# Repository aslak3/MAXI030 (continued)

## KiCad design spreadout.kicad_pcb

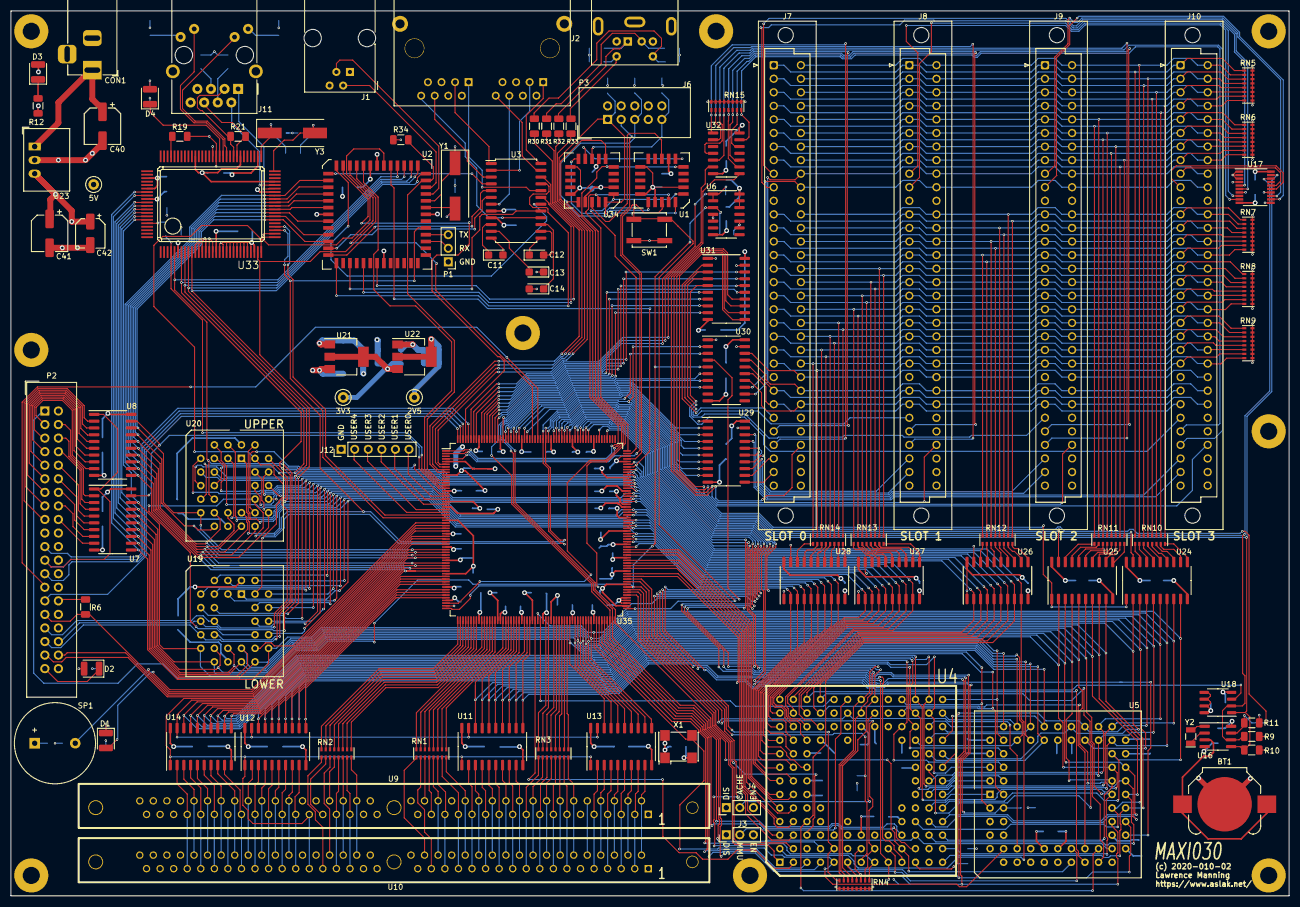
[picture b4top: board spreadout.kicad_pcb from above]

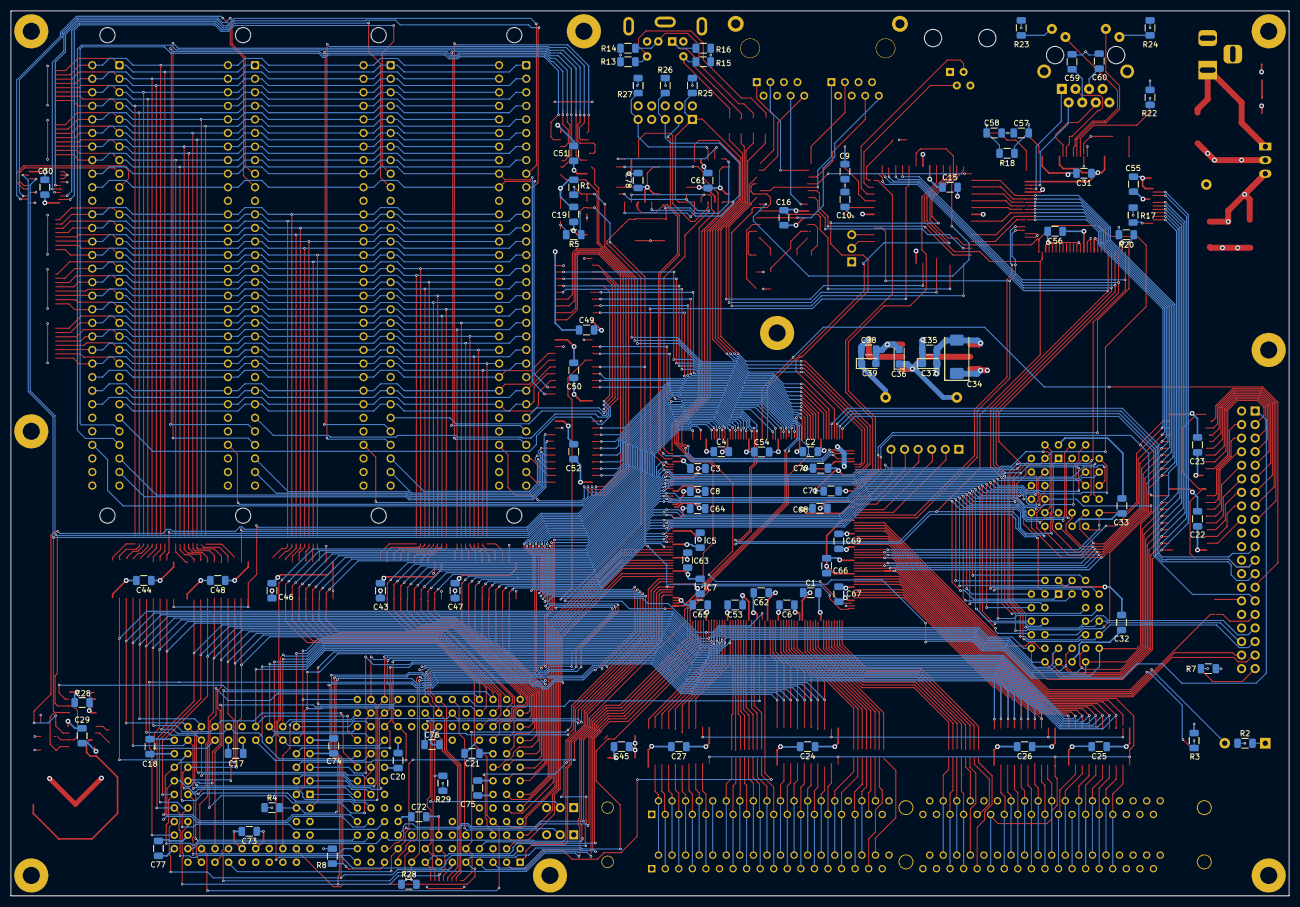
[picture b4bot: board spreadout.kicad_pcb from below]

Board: 4 copper layers, 239.4 x 165.7 mm, 199 parts (93 on the bottom side), 441 nets.

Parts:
BT1: Battery_Cell; BatteryHolder_Keystone_3000_1x12mm
C1, C2, C3, C4, C5, C6, C7, C8, C15, C16, C17, C18, C19, C20, C21, C22, C23, C24, C25, C26, C27, C28, C29, C30, C31, C32, C33, C35, C38, C43, C44, C45, C46, C47, C48, C49, C50, C51, C52, C53, C54, C55, C56, C61, C62, C63, C64, C65, C66, C67, C68, C69, C70, C71, C72, C73, C74, C75, C76, C77, C78: 0.1u; C_1206_3216Metric
C9, C10, C57, C58: 22p; C_1206_3216Metric
C11, C12, C13, C14: 1.0u; CP_EIA-3216-18_Kemet-A
C34: 47u; CP_EIA-7343-15_Kemet-W
C36, C37, C39: 10u; CP_EIA-3216-10_Kemet-I
C40: 470u; CP_Elec_6.3x7.7
C41: 220u; CP_Elec_6.3x7.7
C42: 10u; CP_Elec_5x5.7
C59, C60: 10n; C_1206_3216Metric
CON1: POWERLJACK; BarrelJack_Horizontal
D1: CORELED; LED_1210_3225Metric
D2: IDELED; LED_1210_3225Metric
D3: POWERLED; LED_1210_3225Metric
D4: LED; LED_1210_3225Metric
H1, H2, H3, H4, H5, H6, H7, H8, H9: MountingHole_Pad; MountingHole_3.2mm_M3_Pad
J1: RJ10_KEYBOARD; RJ10
J2: DUALRJ45_RS232; DUALRJ45
J3, J4: Conn_01x03; PinHeader_1x03_P2.54mm_Vertical
J6: Mini-DIN-6; Connector_Mini-DIN_Female_6Pin_2rows
J7, J8, J9, J10: DIN_41612_3x32_MIDI020_EXP; DIN41612_C_2x32_Female_Vertical_THT
J11: RJ45_Amphenol_RJMG1BD3B8K1ANR
J12: Conn_01x06; PinHeader_1x06_P2.54mm_Vertical
P1: TTL_SERIAL; PinHeader_1x03_P2.54mm_Vertical
P2: CONN_02X20_IDE; IDC-Header_2x20_P2.54mm_Vertical
P3: JTAG; IDC-Header_2x05_P2.54mm_Vertical
R1, R4, R5, R6, R8, R9, R10, R11, R13, R14, R15, R16, R28, R29, R34: 4.7K; R_1206_3216Metric
R2, R3, R7, R12, R20, R22, R23, R24, R25, R26, R27: 1K; R_1206_3216Metric
R17: 27K; R_1206_3216Metric
R18: 1M; R_1206_3216Metric
R19: 10K; R_1206_3216Metric
R21: 200; R_1206_3216Metric
R30, R31, R32, R33: 120; R_1206_3216Metric
RN1, RN2, RN3, RN10, RN11, RN12, RN13, RN14: 33; R_Cat16-8
RN4, RN15: 4.7K; R_Cat16-8
RN5, RN6, RN7, RN8, RN9: 10K; R_Cat16-8
SP1: BUZZER; Buzzer_15x7.5RM7.6
SW1: RESETBUTTON; SW_Push_1P1T_NO_CK_KSC6xxJ
TP1: 3V3; TestPoint_Loop_D1.80mm_Drill1.0mm_Beaded
TP2: 2V5; TestPoint_Loop_D1.80mm_Drill1.0mm_Beaded
TP3: 5V; TestPoint_Loop_D1.80mm_Drill1.0mm_Beaded
U1, U34: EPC2; PLCC-20
U2: SC26C94; PLCC-52
U3: MAX238; SOIC-24W_7.5x15.4mm_P1.27mm
U4: MC68030RC; PGA128
U5: 68882; PLCC-68_THT-Socket
U6: 74LS03; SOIC-14_3.9x8.7mm_P1.27mm
U7, U8, U24, U25, U26, U27, U28, U29, U30, U31: 74HCT245; SO-20_5.3x12.6mm_P1.27mm
U9, U10: SIM72Pin; SIMM72Pins
U11, U12, U13, U14: 74HC245; SO-20_5.3x12.6mm_P1.27mm
U16: LM75A; SO-8_3.9x4.9mm_P1.27mm
U17: PCA9544APW; TSSOP-20_4.4x6.5mm_P0.65mm
U18: DS1307Z+; SOIC-8_3.9x4.9mm_P1.27mm
U19, U20: SST39SF040-PC32; PLCC-32_THT-Socket
U21: AZ1117-3.3; SOT-223-3_TabPin2
U22: AZ1117-2.5; SOT-223-3_TabPin2
U23: SR05S05; Converter_DCDC_RECOM_R-78E-0.5_THT
U32: 74LS21; SOIC-14_3.9x8.7mm_P1.27mm
U33: RTL8019AS
U35: EPF10K130EQC240; PQFP-240_32.1x32.1mm_P0.5mm
X1: MPUOSC; Oscillator_SMD_SeikoEpson_SG8002CA-4Pin_7.0x5.0mm
Y1: 7.3728M; Crystal_SMD_HC49-SD
Y2: 32.768; Crystal_SMD_EuroQuartz_EQ161-2Pin_3.2x1.5mm
Y3: 20M; Crystal_SMD_HC49-SD

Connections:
+2V5: C1.1, C3.1, C5.1, C7.1, C38.1, C39.1, C53.1, C62.1, C64.1, C66.1, C68.1, C70.1, TP2.1, U22.2, U35.5, U35.20, U35.27, U35.47, U35.76, U35.89, U35.96, U35.122, U35.130, U35.150, U35.159, U35.170
+3V3: C2.1, C4.1, C6.1, C8.1, C35.1, C36.1, C37.1, C54.1, C61.1, C63.1, C65.1, C67.1, C69.1, C71.1, C78.1, P3.4, R26.1, R27.1, TP1.1, U1.5, U1.14, U1.18, U1.20, U21.2, U22.3, U34.5, U34.14, U34.18, U34.20, U35.16, U35.37, U35.57, U35.59, U35.77, U35.112, U35.140, U35.160, U35.189, U35.205, U35.224
+5VD: C13.1, C15.1, C16.1, C17.1, C18.1, C19.1, C20.1, C21.1, C22.1, C23.1, C24.1, C25.1, C26.1, C27.1, C28.1, C29.1, C30.1, C31.1, C32.1, C33.1, C34.1, C41.1, C42.1, C43.1, C44.1, C45.1, C46.1, C47.1, C48.1, C49.1, C50.1, C51.1, C52.1, C55.1, C56.1, C72.1, C73.1, C74.1, C75.1, C76.1, C77.1, D3.2, J1.1, J3.1, J4.1, J6.4, J7.c11, J7.c32, J8.c11, J8.c32, J9.c11, J9.c32, J10.c11, J10.c32, P2.20, R1.1, R4.1, R5.2, R7.1, R8.1, R9.1, R10.1, R11.1, R13.2, R14.2, R15.2, R16.2, R22.1, R23.2, R24.2, R28.1, R29.1, R34.2, RN4.9, RN4.10, RN4.11, RN4.12, RN4.13, RN4.14, RN4.15, RN4.16, RN5.9, RN5.10, RN5.11, RN5.12, RN5.13, RN5.14, RN5.15, RN5.16, RN6.9, RN6.10, RN6.11, RN6.12, RN6.13, RN6.14, RN6.15, RN6.16, RN7.9, RN7.10, RN7.11, RN7.12, RN7.13, RN7.14, RN7.15, RN7.16, RN8.9, RN8.10, RN8.11, RN8.12, RN8.13, RN8.14, RN8.15, RN8.16, RN9.9, RN9.10, RN9.11, RN9.12, RN9.13, RN9.14, RN9.15, RN9.16, RN15.9, RN15.10, RN15.11, RN15.12, RN15.13, RN15.14, RN15.15, RN15.16, TP3.1, U2.2, U3.9, U4.C6, U4.D4, U4.D10, U4.F2, U4.F11, U4.H3, U4.H11, U4.K4, U4.K10, U4.L6, U5.10, U5.16, U5.17, U5.18, U5.26, U5.27, U5.43, U5.52, U5.53, U5.61, U6.4, U6.5, U6.9, U6.10, U6.12, U6.13, U6.14, U7.20, U8.20, U9.10, U9.30, U9.59, U10.10, U10.30, U10.59, U11.20, U12.20, U13.20, U14.20, U16.5, U16.6, U16.7, U16.8, U17.4, U17.7, U17.11, U17.14, U17.20, U18.8, U19.32, U20.32, U21.3, U23.3, U24.20, U25.20, U26.1, U26.20, U27.1, U27.20, U28.1, U28.20, U29.1, U29.20, U30.1, U30.20, U31.1, U31.20, U32.14, U33.6, U33.15, U33.16, U33.17, U33.31, U33.32, U33.47, U33.57, U33.65, U33.70, U33.89, X1.1, X1.4
/FPGA/USER0: J12.6, U35.18
/FPGA/USER1: J12.5, U35.19
/FPGA/USER2: J12.4, U35.21
/FPGA/USER3: J12.3, U35.23
/FPGA/USER4: J12.2, U35.24
/IDE/IDED0: P2.4, U7.2
/IDE/IDED1: P2.6, U7.3
/IDE/IDED2: P2.8, U7.4
/IDE/IDED3: P2.10, U7.5
/IDE/IDED4: P2.12, U7.6
/IDE/IDED5: P2.14, U7.7
/IDE/IDED6: P2.16, U7.8
/IDE/IDED7: P2.18, U7.9
/IDE/IDED8: P2.17, U8.2
/IDE/IDED9: P2.15, U8.3
/IDE/IDED10: P2.13, U8.4
/IDE/IDED11: P2.11, U8.5
/IDE/IDED12: P2.9, U8.6
/IDE/IDED13: P2.7, U8.7
/IDE/IDED14: P2.5, U8.8
/IDE/IDED15: P2.3, U8.9
/SIMM/SD0: U9.2, U10.2, U13.9
/SIMM/SD1: U9.4, U10.4, U13.7
/SIMM/SD2: U9.6, U10.6, U13.5
/SIMM/SD3: U9.8, U10.8, U13.3
/SIMM/SD4: U9.20, U10.20, U11.9
/SIMM/SD5: U9.22, U10.22, U11.7
/SIMM/SD6: U9.24, U10.24, U11.5
/SIMM/SD7: U9.26, U10.26, U11.3
/SIMM/SD8: U9.49, U10.49, U12.9
/SIMM/SD9: U9.51, U10.51, U12.7
/SIMM/SD10: U9.53, U10.53, U12.5
/SIMM/SD11: U9.55, U10.55, U12.3
/SIMM/SD12: U9.57, U10.57, U14.9
/SIMM/SD13: U9.61, U10.61, U14.6
/SIMM/SD14: U9.63, U10.63, U14.4
/SIMM/SD15: U9.65, U10.65, U14.2
/SIMM/SD16: U9.3, U10.3, U13.8
/SIMM/SD17: U9.5, U10.5, U13.6
/SIMM/SD18: U9.7, U10.7, U13.4
/SIMM/SD19: U9.9, U10.9, U13.2
/SIMM/SD20: U9.21, U10.21, U11.8
/SIMM/SD21: U9.23, U10.23, U11.6
/SIMM/SD22: U9.25, U10.25, U11.4
/SIMM/SD23: U9.27, U10.27, U11.2
/SIMM/SD24: U9.50, U10.50, U12.8
/SIMM/SD25: U9.52, U10.52, U12.6
/SIMM/SD26: U9.54, U10.54, U12.4
/SIMM/SD27: U9.56, U10.56, U12.2
/SIMM/SD28: U9.58, U10.58, U14.8
/SIMM/SD29: U9.60, U10.60, U14.7
/SIMM/SD30: U9.62, U10.62, U14.5
/SIMM/SD31: U9.64, U10.64, U14.3
A0: U2.51, U4.A2, U26.9, U35.174
A1: U2.50, U4.C4, U5.25, U19.12, U20.12, U26.8, U33.5, U35.173
A2: P2.35, U2.49, U4.D13, U5.24, U19.11, U20.11, U26.7, U33.7, U35.172
A3: P2.33, U2.48, U4.D12, U5.23, U19.10, U20.10, U26.6, U33.8, U35.171
A4: P2.36, U2.47, U4.C13, U5.22, U19.9, U20.9, U26.5, U33.9, U35.169
A5: U2.46, U4.C12, U19.8, U20.8, U26.4, U33.10, U35.168
A6: U4.D11, U19.7, U20.7, U26.3, U35.167
A7: U4.B13, U19.6, U20.6, U26.2, U35.166
A8: U4.B12, U19.5, U20.5, U27.9, U35.164
A9: U4.C11, U19.27, U20.27, U27.8, U35.163
A10: U4.A13, U19.26, U20.26, U27.7, U35.162
A11: U4.C10, U19.23, U20.23, U27.6, U35.161
A12: U4.B11, U19.25, U20.25, U27.5, U35.158
A13: U4.A12, U19.4, U20.4, U27.4, U35.157
A14: U4.B10, U19.28, U20.28, U27.3, U35.156
A15: U4.A11, U19.29, U20.29, U27.2, U35.154
A16: U4.B9, U19.3, U20.3, U28.9, U35.153
A17: U4.A10, U19.2, U20.2, U28.8, U35.152
A18: U4.C8, U19.30, U20.30, U28.7, U35.151
A19: U4.A9, U19.1, U20.1, U28.6, U35.149
A20: U4.B8, U28.5, U35.148
A21: U4.A8, U28.4, U35.147
A22: U4.B7, U28.3, U35.146
A23: U4.A7, U28.2, U35.144
A24: U4.A6, U35.143
A25: U4.B6, U35.142
A26: U4.A5, U35.141
A27: U4.B5, U35.139
A28: U4.A4, U35.138
A29: U4.B4, U35.137
A30: U4.A3, U35.136
A31: U4.B3, U35.134
BUZZER: SP1.2, U35.30
CFCLOCK: U1.4, U34.4, U35.179
CFCONFIG: SW1.1, U34.13, U35.121
CFDATA: U1.2, U34.2, U35.180
CFDONE: U34.9, U35.2
CFSTATUS: U1.8, U34.8, U35.60
CFTOCORE: U1.1, U35.177
CORETOHEADER: P3.3, U35.4
CTSA232: J2.A8, U3.23
CTSB232: J2.B8, U3.16
D0: U4.K13, U5.3, U11.18, U35.80
D1: U4.K12, U5.2, U11.17, U35.81
D2: U4.L13, U5.1, U11.16, U35.82
D3: U4.M13, U5.68, U11.15, U35.83
D4: U4.L12, U5.67, U11.14, U35.84
D5: U4.K11, U5.66, U11.13, U35.86
D6: U4.M12, U5.65, U11.12, U35.87
D7: U4.L11, U5.64, U11.11, U35.88
D8: U4.N13, U5.62, U12.18, U35.48
D9: U4.M11, U5.60, U12.17, U35.49
D10: U4.L10, U5.59, U12.16, U35.50
D11: U4.N12, U5.58, U12.15, U35.51
D12: U4.M10, U5.57, U12.14, U35.53
D13: U4.N11, U5.56, U12.13, U35.54
D14: U4.M9, U5.55, U12.12, U35.55
D15: U4.N10, U5.54, U12.11, U35.56
D16: U4.N9, U5.50, U7.18, U13.18, U19.13, U24.2, U33.95, U35.103
D17: U4.M8, U5.49, U7.17, U13.17, U19.14, U24.3, U33.94, U35.105
D18: U4.N8, U5.48, U7.16, U13.16, U19.15, U24.4, U33.93, U35.106
D19: U4.N7, U5.47, U7.15, U13.15, U19.17, U24.5, U33.92, U35.107
D20: U4.M7, U5.46, U7.14, U13.14, U19.18, U24.6, U33.91, U35.108
D21: U4.N6, U5.45, U7.13, U13.13, U19.19, U24.7, U33.90, U35.109
D22: U4.M6, U5.44, U7.12, U13.12, U19.20, U24.8, U33.88, U35.110
D23: U4.N5, U5.42, U7.11, U13.11, U19.21, U24.9, U33.87, U35.111
D24: U2.18, U4.M5, U5.40, U8.18, U14.18, U20.13, U25.2, U33.36, U35.38
D25: U2.17, U4.N4, U5.39, U8.17, U14.17, U20.14, U25.3, U33.37, U35.39
D26: U2.15, U4.N3, U5.38, U8.16, U14.16, U20.15, U25.4, U33.38, U35.40
D27: U2.13, U4.M4, U5.37, U8.15, U14.15, U20.17, U25.5, U33.39, U35.41
D28: U2.12, U4.N2, U5.36, U8.14, U14.14, U20.18, U25.6, U33.40, U35.43
D29: U2.11, U4.M3, U5.35, U8.13, U14.13, U20.19, U25.7, U33.41, U35.44
D30: U2.10, U4.L4, U5.34, U8.12, U14.12, U20.20, U25.8, U33.42, U35.45
D31: U2.9, U4.N1, U5.33, U8.11, U14.11, U20.21, U25.9, U33.43, U35.46
ETHINT: R20.2, U33.4, U35.14
EXPA0: J7.a12, J8.a12, J9.a12, J10.a12, RN7.1, RN12.9
EXPA1: J7.c12, J8.c12, J9.c12, J10.c12, RN7.2, RN12.10
EXPA2: J7.a13, J8.a13, J9.a13, J10.a13, RN7.3, RN12.11
EXPA3: J7.c13, J8.c13, J9.c13, J10.c13, RN7.4, RN12.12
EXPA4: J7.a14, J8.a14, J9.a14, J10.a14, RN7.5, RN12.13
EXPA5: J7.c14, J8.c14, J9.c14, J10.c14, RN7.6, RN12.14
EXPA6: J7.a15, J8.a15, J9.a15, J10.a15, RN7.7, RN12.15
EXPA7: J7.c15, J8.c15, J9.c15, J10.c15, RN7.8, RN12.16
EXPA8: J7.a16, J8.a16, J9.a16, J10.a16, RN8.1, RN13.9
EXPA9: J7.c16, J8.c16, J9.c16, J10.c16, RN8.2, RN13.10
EXPA10: J7.a17, J8.a17, J9.a17, J10.a17, RN8.3, RN13.11
EXPA11: J7.c17, J8.c17, J9.c17, J10.c17, RN8.4, RN13.12
EXPA12: J7.a18, J8.a18, J9.a18, J10.a18, RN8.5, RN13.13
EXPA13: J7.c18, J8.c18, J9.c18, J10.c18, RN8.6, RN13.14
EXPA14: J7.a19, J8.a19, J9.a19, J10.a19, RN8.7, RN13.15
EXPA15: J7.c19, J8.c19, J9.c19, J10.c19, RN8.8, RN13.16
EXPA16: J7.a20, J8.a20, J9.a20, J10.a20, RN9.1, RN14.9
EXPA17: J7.c20, J8.c20, J9.c20, J10.c20, RN9.2, RN14.10
EXPA18: J7.a21, J8.a21, J9.a21, J10.a21, RN9.3, RN14.11
EXPA19: J7.c21, J8.c21, J9.c21, J10.c21, RN9.4, RN14.12
EXPA20: J7.a22, J8.a22, J9.a22, J10.a22, RN9.5, RN14.13
EXPA21: J7.c22, J8.c22, J9.c22, J10.c22, RN9.6, RN14.14
EXPA22: J7.a23, J8.a23, J9.a23, J10.a23, RN9.7, RN14.15
EXPA23: J7.c23, J8.c23, J9.c23, J10.c23, RN9.8, RN14.16
EXPD16: J7.a1, J8.a1, J9.a1, J10.a1, RN5.1, RN10.16
EXPD17: J7.c1, J8.c1, J9.c1, J10.c1, RN5.2, RN10.15
EXPD18: J7.a2, J8.a2, J9.a2, J10.a2, RN5.3, RN10.14
EXPD19: J7.c2, J8.c2, J9.c2, J10.c2, RN5.4, RN10.13
EXPD20: J7.a3, J8.a3, J9.a3, J10.a3, RN5.5, RN10.12
EXPD21: J7.c3, J8.c3, J9.c3, J10.c3, RN5.6, RN10.11
EXPD22: J7.a4, J8.a4, J9.a4, J10.a4, RN5.7, RN10.10
EXPD23: J7.c4, J8.c4, J9.c4, J10.c4, RN5.8, RN10.9
EXPD24: J7.a5, J8.a5, J9.a5, J10.a5, RN6.1, RN11.16
EXPD25: J7.c5, J8.c5, J9.c5, J10.c5, RN6.2, RN11.15
EXPD26: J7.a6, J8.a6, J9.a6, J10.a6, RN6.3, RN11.14
EXPD27: J7.c6, J8.c6, J9.c6, J10.c6, RN6.4, RN11.13
EXPD28: J7.a7, J8.a7, J9.a7, J10.a7, RN6.5, RN11.12
EXPD29: J7.c7, J8.c7, J9.c7, J10.c7, RN6.6, RN11.11
EXPD30: J7.a8, J8.a8, J9.a8, J10.a8, RN6.7, RN11.10
EXPD31: J7.c8, J8.c8, J9.c8, J10.c8, RN6.8, RN11.9
EXPMPUCLK: J7.a25, J8.a25, J9.a25, J10.a25, U30.16
EXPR~W: J7.c26, J8.c26, J9.c26, J10.c26, U30.14
EXPSCLE0: J7.a9, U17.6
EXPSCLE1: J8.a9, U17.9
EXPSCLE2: J9.a9, U17.13
EXPSCLE3: J10.a9, U17.16
EXPSDAE0: J7.a10, U17.5
EXPSDAE1: J8.a10, U17.8
EXPSDAE2: J9.a10, U17.12
EXPSDAE3: J10.a10, U17.15
FC0: U4.D2, U35.113
FC1: U4.C1, U35.114
FC2: U4.D1, U35.115
GNDA: BT1.2, C1.2, C2.2, C3.2, C4.2, C5.2, C6.2, C7.2, C8.2, C9.2, C10.2, C14.2, C15.2, C16.2, C17.2, C18.2, C19.2, C20.2, C21.2, C22.2, C23.2, C24.2, C25.2, C26.2, C27.2, C28.2, C29.2, C30.2, C31.2, C32.2, C33.2, C34.2, C35.2, C36.2, C37.2, C38.2, C39.2, C40.2, C41.2, C42.2, C43.2, C44.2, C45.2, C46.2, C47.2, C48.2, C49.2, C50.2, C51.2, C52.2, C53.2, C54.2, C55.2, C56.2, C57.1, C58.1, C59.2, C60.2, C61.2, C62.2, C63.2, C64.2, C65.2, C66.2, C67.2, C68.2, C69.2, C70.2, C71.2, C72.2, C73.2, C74.2, C75.2, C76.2, C77.2, C78.2, CON1.2, CON1.3, H1.1, H2.1, H3.1, H4.1, H5.1, H6.1, H7.1, H8.1, H9.1, J1.4, J2.A4, J2.A5, J2.B4, J2.B5, J2.GND, J3.3, J4.3, J6.3, J7.a11, J7.a32, J8.a11, J8.a32, J9.a11, J9.a32, J10.a11, J10.a32, J11.13, J11.R8, J12.1, P1.1, P2.2, P2.19, P2.22, P2.24, P2.26, P2.30, P2.40, P3.2, P3.10, R2.1, R3.1, R6.1, R12.2, R17.1, R19.1, R20.1, R25.2, SW1.2, U1.10, U2.1, U2.14, U2.28, U2.40, U3.8, U4.C5, U4.C7, U4.C9, U4.E3, U4.E11, U4.F3, U4.G3, U4.G11, U4.J3, U4.J11, U4.L5, U4.L7, U4.L8, U4.L9, U5.5, U5.6, U5.7, U5.8, U5.9, U5.12, U5.14, U5.19, U5.30, U5.41, U5.51, U5.63, U6.7, U7.10, U8.10, U9.1, U9.39, U9.72, U10.1, U10.39, U10.72, U11.10, U12.10, U13.10, U14.10, U16.4, U17.1, U17.2, U17.3, U17.10, U18.4, U19.16, U20.16, U21.1, U22.1, U23.2, U24.10, U25.10, U26.10, U26.19, U27.10, U27.19, U28.10, U28.19, U29.10, U29.19, U30.10, U30.19, U31.10, U31.19, U32.7, U33.11, U33.12, U33.13, U33.14, U33.18, U33.19, U33.20, U33.21, U33.22, U33.23, U33.24, U33.25, U33.26, U33.27, U33.28, U33.44, U33.52, U33.64, U33.83, U33.86, U34.10, U35.10, U35.22, U35.32, U35.42, U35.52, U35.69, U35.85, U35.93, U35.104, U35.123, U35.124, U35.125, U35.135, U35.145, U35.155, U35.165, U35.176, U35.178, U35.197, U35.216, U35.232, X1.2
HEADERTOCF: P3.9, R27.2, U34.11
IDEIRQ: P2.31, R6.2, U35.31
LED: D1.2, U35.29
MPUCLK: U4.E1, U5.11, U30.4, U35.91, X1.3
unnamed: BT1.1, U18.3
unnamed: C9.1, U2.42, Y1.1
unnamed: C10.1, U2.41, Y1.2
unnamed: C11.1, U3.10
unnamed: C11.2, U3.12
unnamed: C12.1, U3.13
unnamed: C12.2, U3.14
unnamed: C13.2, U3.11
unnamed: C14.1, U3.15
unnamed: C40.1, CON1.1, U23.1
unnamed: C57.2, R18.2, U33.51, Y3.1
unnamed: C58.2, R18.1, U33.50, Y3.2
unnamed: C59.1, J11.R4
unnamed: C60.1, J11.R5
unnamed: D1.1, R3.2
unnamed: D2.1, P2.39
unnamed: D2.2, R7.2
unnamed: D3.1, R12.1
unnamed: D4.1, U33.63
unnamed: D4.2, R22.2
unnamed: J1.2, U2.44
unnamed: J1.3, U2.43
unnamed: J6.1, R16.1, R32.1
unnamed: J6.2, R14.1, R31.2
unnamed: J6.5, R15.1, R33.1
unnamed: J6.6, R13.1, R30.2
unnamed: J11.L1, R24.1
unnamed: J11.L2, U33.62
unnamed: J11.L3, U33.61
unnamed: J11.L4, R23.1
unnamed: J11.R1, U33.45
unnamed: J11.R2, U33.46
unnamed: J11.R3, R21.1, U33.59
unnamed: J11.R6, R21.2, U33.58
unnamed: P1.2, U2.36
unnamed: P1.3, U2.37
unnamed: R2.2, SP1.1
unnamed: R17.2, U33.96
unnamed: R19.2, U33.77
unnamed: RN1.1, U35.79
unnamed: RN1.2, U35.78
unnamed: RN1.3, U35.75
unnamed: RN1.4, U35.74
unnamed: RN1.5, U35.73
unnamed: RN1.6, U35.72
unnamed: RN1.7, U35.71
unnamed: RN1.8, U35.70
unnamed: RN2.1, U35.68
unnamed: RN2.2, U35.67
unnamed: RN2.3, U35.66
unnamed: RN2.4, U35.65
unnamed: RN2.5, U35.64
unnamed: RN2.6, U35.63
unnamed: RN2.7, U35.62
unnamed: RN2.8, U35.61
unnamed: RN3.1, U35.102
unnamed: RN3.2, U35.101
unnamed: RN3.3, U35.100
unnamed: RN3.4, U35.99
unnamed: RN3.5, U35.98
unnamed: RN3.6, U35.97
unnamed: RN3.7, U35.95
unnamed: RN3.8, U35.94
unnamed: RN10.1, U24.18
unnamed: RN10.2, U24.17
unnamed: RN10.3, U24.16
unnamed: RN10.4, U24.15
unnamed: RN10.5, U24.14
unnamed: RN10.6, U24.13
unnamed: RN10.7, U24.12
unnamed: RN10.8, U24.11
unnamed: RN11.1, U25.18
unnamed: RN11.2, U25.17
unnamed: RN11.3, U25.16
unnamed: RN11.4, U25.15
unnamed: RN11.5, U25.14
unnamed: RN11.6, U25.13
unnamed: RN11.7, U25.12
unnamed: RN11.8, U25.11
unnamed: RN12.1, U26.18
unnamed: RN12.2, U26.17
unnamed: RN12.3, U26.16
unnamed: RN12.4, U26.15
unnamed: RN12.5, U26.14
unnamed: RN12.6, U26.13
unnamed: RN12.7, U26.12
unnamed: RN12.8, U26.11
unnamed: RN13.1, U27.18
unnamed: RN13.2, U27.17
unnamed: RN13.3, U27.16
unnamed: RN13.4, U27.15
unnamed: RN13.5, U27.14
unnamed: RN13.6, U27.13
unnamed: RN13.7, U27.12
unnamed: RN13.8, U27.11
unnamed: RN14.1, U28.18
unnamed: RN14.2, U28.17
unnamed: RN14.3, U28.16
unnamed: RN14.4, U28.15
unnamed: RN14.5, U28.14
unnamed: RN14.6, U28.13
unnamed: RN14.7, U28.12
unnamed: RN14.8, U28.11
unnamed: U1.9, U34.12
unnamed: U1.11, U34.1
unnamed: U2.7, U3.18
unnamed: U2.8, U3.4
unnamed: U2.19, U3.6
unnamed: U2.20, U3.5
unnamed: U2.21, U3.21
unnamed: U2.23, U3.17
unnamed: U2.25, U3.19
unnamed: U2.27, U3.22
unnamed: U18.1, Y2.2
unnamed: U18.2, Y2.1
PS2ACLK: R33.2, U35.6
PS2ADATA: R32.2, U35.7
PS2BCLK: R30.1, U35.9
PS2BDATA: R31.1, U35.8
RESET: U2.38, U33.33, U35.26
RTCSQWAVE: R11.2, U18.7, U35.206
RTSA232: J2.A1, U3.24
RTSB232: J2.B1, U3.20
RXA232: J2.A6, U3.7
RXB232: J2.B6, U3.3
R~W: U4.L3, U5.28, U30.6, U35.118
SA0: RN3.16, U9.12, U10.12
SA1: RN3.15, U9.13, U10.13
SA2: RN3.14, U9.14, U10.14
SA3: RN3.13, U9.15, U10.15
SA4: RN3.12, U9.16, U10.16
SA5: RN3.11, U9.17, U10.17
SA6: RN3.10, U9.18, U10.18
SA7: RN1.16, U9.28, U10.28
SA8: RN1.14, U9.31, U10.31
SA9: RN1.13, U9.32, U10.32
SA10: RN3.9, U9.19, U10.19
SA11: RN1.15, U9.29, U10.29
SCL: R9.2, U16.2, U17.18, U18.6, U35.202
SDA: R10.2, U16.1, U17.19, U18.5, U35.201
SIZ0: U4.L2, U35.116
SIZ1: U4.K3, U35.117
SYSCLEAR: R1.2, U6.1, U6.2, U35.233
TCK: P3.1, R25.1, U1.3, U34.3, U35.1
TEMPALERT: U16.3, U35.133
TMS: P3.5, R26.2, U1.19, U34.19, U35.58
TXA232: J2.A3, U3.2
TXB232: J2.B3, U3.1
~AS: U4.J2, U5.21, U30.7, U35.119
~AVEC: RN4.8, U4.E2, U35.194
~BERR: RN4.1, U4.H1, U35.132
~BERRE: U32.8, U35.235
~BG: U4.B2, U35.127
~BGACK: U4.C3, U35.128
~BR: U4.A1, U35.126
~CAS0: RN2.16, U9.40, U10.40
~CAS1: RN2.13, U9.43, U10.43
~CAS2: RN2.15, U9.41, U10.41
~CAS3: RN2.14, U9.42, U10.42
~CBACK: R28.2, U4.J1, U35.196
~CBREQ: U4.K1, U35.195
~CDIS: J4.2, U4.H12
~CIIN: R8.2, U4.L1, U35.198
~DS: U4.K2, U5.20, U30.8, U35.120
~DSACK0: RN4.4, U4.F1, U5.31, U35.192
~DSACK1: RN4.3, U4.G2, U5.32, U35.191
~ETHCS: U33.34, U35.25
~EXPAS: J7.c10, J8.c10, J9.c10, J10.c10, U30.13
~EXPBERRE0: J7.a28, RN15.5, U32.9
~EXPBERRE1: J8.a28, RN15.6, U32.10
~EXPBERRE2: J9.a28, RN15.7, U32.12
~EXPBERRE3: J10.a28, RN15.8, U32.13
~EXPDS: J7.c9, J8.c9, J9.c9, J10.c9, U30.12
~EXPIACKE0: J7.c29, U31.14
~EXPIACKE1: J8.c29, U31.13
~EXPIACKE2: J9.c29, U31.12
~EXPIACKE3: J10.c29, U31.11
~EXPINTE0: J7.a27, U31.2
~EXPINTE1: J8.a27, U31.3
~EXPINTE2: J9.a27, U31.4
~EXPINTE3: J10.a27, U31.5
~EXPLCSE0: J7.a30, U29.12
~EXPLCSE1: J8.a30, U29.14
~EXPLCSE2: J9.a30, U29.16
~EXPLCSE3: J10.a30, U29.18
~EXPREAD: J7.c24, J8.c24, J9.c24, J10.c24, U30.18
~EXPRESET: J7.a26, J8.a26, J9.a26, J10.a26, U30.15
~EXPUCSE0: J7.a31, U29.11
~EXPUCSE1: J8.a31, U29.13
~EXPUCSE2: J9.a31, U29.15
~EXPUCSE3: J10.a31, U29.17
~EXPWAITE0: J7.a29, RN15.1, U32.1
~EXPWAITE1: J8.a29, RN15.2, U32.2
~EXPWAITE2: J9.a29, RN15.3, U32.4
~EXPWAITE3: J10.a29, RN15.4, U32.5
~EXPWRITE: J7.c25, J8.c25, J9.c25, J10.c25, U30.17
~FPUCS: U5.29, U35.199
~FPUSENSE: R4.2, U5.4, U35.200
~HALT: RN4.2, U4.H2, U35.131
~IACKE0: U31.6, U35.227
~IACKE1: U31.7, U35.226
~IACKE2: U31.8, U35.225
~IACKE3: U31.9, U35.223
~IDE1CS: P2.37, U35.34
~IDE3CS: P2.38, U35.33
~IDECS: U7.19, U8.19, U35.15
~IDEDMAACK: P2.29, U35.240
~IDEDMAREQ: P2.21, U35.236
~IDEREAD: P2.25, U35.239
~IDEREADY: P2.27, U35.210
~IDEWRITE: P2.23, U7.1, U8.1, U35.238
~INTE0: U31.18, U35.231
~INTE1: U31.17, U35.230
~INTE2: U31.16, U35.229
~INTE3: U31.15, U35.228
~IPEND: U4.E13, U35.92
~IPL0: RN4.5, U4.H13, U35.175
~IPL1: RN4.7, U4.G13, U35.184
~IPL2: RN4.6, U4.G12, U35.187
~LCSE0: U29.8, U35.215
~LCSE1: U29.6, U35.218
~LCSE2: U29.4, U35.220
~LCSE3: U29.2, U35.222
~LEXP: U24.19, U35.203
~LROM: U19.22, U35.28
~MMUDIS: J3.2, U4.F13
~QUART: U2.3, U35.13
~QUARTDTACK: U2.5, U35.212
~QUARTIACK: U2.6, U35.237
~QUARTIRQ: R34.1, U2.45, U35.12
~RASA0: RN2.11, U10.44
~RASA1: RN2.9, U10.45
~RASA2: RN1.9, U10.34
~RASA3: RN1.10, U10.33
~RASB0: RN2.12, U9.44
~RASB1: RN2.10, U9.45
~RASB2: RN1.11, U9.34
~RASB3: RN1.12, U9.33
~READ: U2.4, U19.24, U20.24, U24.1, U25.1, U30.2, U33.29, U35.207
~RESET: P2.1, R5.1, U4.F12, U5.13, U6.3, U30.5, U35.129
~RMC: U4.B1, U35.90
~SIMM: U11.19, U12.19, U13.19, U14.19, U35.36
~SIMMWE: U9.47, U10.47, U11.1, U12.1, U13.1, U14.1, U35.35
~STERM: R29.2, U4.G1, U35.193
~UCSE0: U29.9, U35.214
~UCSE1: U29.7, U35.217
~UCSE2: U29.5, U35.219
~UCSE3: U29.3, U35.221
~UEXP: U25.19, U35.204
~UROM: U20.22, U35.17
~WAITE: U32.6, U35.234
~WRITE: U2.52, U19.31, U20.31, U30.3, U33.30, U35.208

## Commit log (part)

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2022-06-17 Added MAXI030 schematic, PCB and VHDL files
    TODO: Documentaiton...
2022-06-17 Resize and rotate main image
2022-06-17 Intiial doc
2022-06-18 Extended and improved the documentation
    Also added Linux "build a debian" script.
2022-06-18 Added expansion cards, with some doc updates
    Removed the old KiCAD 4 format files
2022-06-24 Just twiddling/extending the docs
2022-06-24 Updated the schematic
    Noticed it wasn't quite the one the final PCBs were based off.
2022-07-15 Added a LICENCE (GPLv2)
2022-08-10 Added the MAXI030 bom, which somehow got left off
2025-10-03 Working on a rewrite of the FPGA glue logic in Verilog
    Builds via SSH to Win7 VM. Not ideal, but no other choice with such
    old FPGAs. This will mean I can glue in iVerilog testbenches and other
    nice and modern things and hoepfully hardly ever have to go near the awful
    Quartus UI. But for now it's just a toplevel entity... er module and a
    module that flashes the LED.
2025-10-06 Checkpoint: the board is running!
    Rebuilt the bootloader and monitor with updated addressing and
    linker script. Running out the SRAM card in slot 0 for now. UART and
    IDE seem to be working. No interrupts, timers, PS/2 or any of the
    FPGA peripherals are available. Except the LED, which works. :)
    Next up will probably be to port/rewrite the old DRAM controller.
    Verilator in lint mode is used as a sanity check before passing it to
2025-10-07 Added 32 bit FPGA registers
    Might be useful one day. Finally tested the other 24 bits of databus
    between the processor and the FPGA and have no problems. The previous
    VHDL glue only ever had 8 bits used. For consistency will probably
    add a window for 16 bit registers too, though it will need some address
    reunumbering as currently slot 0 is at 40000000. Currently we have:
    00 - SIMM 32 bit (but SLOT0 is currently sat here)
2025-10-08 Fun with renumbering everything
    40 8 bit
    80 16 bit
    c0 32 bit
    The FPGA registers are at the start, the devices start 10 along, so
    SLOTs are at 90, 91 etc, the QUART is at 50, etc. SIMM is at d0 so I
    can work on a memory controller. Also made port_width use the same
2025-10-09 Added a basic DRAM controller and a simple testbench
    Direct port of the existing VHDL one. Now to make it better.
    Testbech just makes waveforms at the moment.
2025-10-09 Drop the non bit position `defines for chip selects
    This was prone to typos and I spent 15 mins finding one with the SIMM
    controller. Just use 1 << FOO_POS in the addr decoder. May drop _POS
    as a suffix, not sure yet.
2025-10-09 Made the interface to the SIMM controller a bit simpler
    Pass in read/write and the chip select. DS is not needed as read and
    write are gated by it. Generate the SIMM write signal from write and
    the chip select.
2025-10-09 Seems to result in dodgy data, going for something simpler for now
    Revert "Made the interface to the SIMM controller a bit simpler"
    This reverts commit 187eabded1bac75280163b9cab7e48f0fa083bc8.
2025-10-10 Remove AS from controller input
    Wait on CS instead for the end of the waitstate.
2025-10-10 Fix tabs to spaces and crlf to cr
    Dunno how the tabs got in there.
2025-10-11 Added basic interrupt routing and a timer
    The timer has two registers, a starting count (32 bit) and a control
    register (8 bit). Currently the control register is erroniously
    readable. The interrupts are basic autovectoring, as they were before,
    and default to being masked/disabled.
    For consistency, all registers are passed in as 32 bit to the subsytem
    (LED, timer, whatever). This is done because some subsystems, like
2025-10-16 Add a Makefile for building the VHDL glue with a remote Quartus
2026-01-15 Made SIMM controller suport two sticks of 32MB
    Also converted every file to unix format text.
2026-01-25 MAXI030Core: Display the fMax from the summary
2026-01-25 Switchd to SPEED optimisation to match VHDL
2026-02-03 verilog: Added an SPI interface and some other tweaks
    Made the memory map match the VHDL in an attempt to get this to start with
    the SIMM acting as main memory.
2026-02-26 Fixed the SIMM controller to work with a clockless decoder
    This took a lot of experimination, but finally I have the board
    running off the Verilog glue. It's not complete at all, and is eg.
    missing a buzzer, PS/2 interface, I2C controlller, etc. But it's
    progress.
    Have also added a "BROM", a ROM in the FPGA. I cannot get it to use
    the BRAM but, and it shows how sizeable the FPGA is, all 2KBbytes
2026-02-27 Added beeper (renamed tonegen) and 32 bit registers
    This is an interim memory map. Will renumber a few things once I have all
    the peripherals moved across. For now the timer (with interrupts) is
    working and I've added a tone generator, borrowing the code from my
    softcore project. It therefore has a duration register and will
    eventuallyl be useable under interrupt control.
    The width of the FPGA register is encoded in [15:8], which has the
2026-02-27 Added the PS/2 and I2C controllers, from the softcore project
    Not much testing done yet. fMax has taken a battering, especially with the
    i2c controller. Might have to look at making it more efficent. Board boots
    fine still though.
2026-02-28 Making the led controller an "interface"
    There's no controller here, the led state is manipulated by the interface
    directly. But it's at least consistent in the way readback is done.
2026-03-02 Moved the timer into an "interface"
    Made the control register 32 bits just to keep all registers within a
    single "part" the same width.
2026-03-02 Moved the interrupt processing into an "interface"
    This includes the piority encoder. But I've decided that everything that
    directly operates under processor control should be encapsulated into
    an "interface". The stuff that isn't are modules that operate independant
    of read and writes from the processor, like address decoding, the byte
    selector etc.
    Made the interrupt mask register 16 bit, though only 5 are used
2026-03-02 I2C: Fix the bit posistion on the last_byte control bit
    I2C now works nicely.
2026-03-02 Just minor cleanups
    Ordering of reset/clock to be consistant (reset is always first) and
    many indenting fixes.
2026-04-14 Added an initial go at a DMAC
    Supports copies from word and long ports to long ports. Transfers up to
    64KB.
    Far from finished. The bulk of the time was spent figuring out the bus
    mastering and creating an internal bus that address decoding and other
    parts of the glue use instead of just using the external pins.
    One thing to do before merging this with master is to redo the README.md
2026-06-09 Started on a Verilog display controller
